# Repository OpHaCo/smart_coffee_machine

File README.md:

# Coffee machine Hack

Project has been done in Amiqual4Home Equipex Creativity Lab - https://amiqual4home.inria.fr/
We worked with ENSIMAG students of ["café sourire project"](http://fablab.ensimag.fr/index.php/Machine_%C3%A0_caf%C3%A9_%22sourire%22_:_Machine_connect%C3%A9_qui_offre_des_caf%C3%A9s_aux_personnes_souriantes)  

*To hack : Saeco Intelia Coffee Machine*

## **Description**
**You purchased a Saeco Intelia coffee machine. You are very satisfied with it, but you would like to make your coffee from your bedroom just after you wake up...** 

Some other products can do it for you : http://smarter.am/coffee/ . But with Smarter coffee machine you will have to change Coffee filter each time you get a coffee. With an "automatic" coffee machine such as Intelia, coffee grounds are pushed to a compartment : you can do several coffee only by pushing buttons and putting a cup of coffee.

Best choice for a super automatic & connected coffee machine is Philips Saeco Gran Baristo Avanti. It is connected over bluetooth. Due to bluetooth range limitations, you won't be able to do your coffee from your bedroom. It costs 2500$!!  
[Fortune and smart coffee maker](http://fortune.com/2015/12/24/smart-coffee-maker/)

With this project you will :
 *  **make your automatic coffee machine smarter adding means to control it from anywhere**  e.g. : 
    *  prepare coffee for tomorrow morning at 8AM 
    *  give a vocal command to your smartphone that will make your coffee
    *  using a camera (refer 'Used in projects' section) to deliver coffee to identified users (refer example of 'café sourire' ) 

*Café Sourire*

 * **get coffee machine statistics such as number of coffee per day...**

*Coffee metrics*
 
 * **improve some existing parts**
    * add a bigger coffee compartment (TODO)
    * add cup detection (TODO)
    * cup distribution (TODO)

## **Prerequisities**
 * **saeco intelia coffee machine** : https://www.amazon.com/Philips-Saeco-Intelia-Automatic-Espresso/dp/B00B5M3G26
 * some screws to open coffee machine
 * An external board connected to Coffee Machine front side daugther board : 
   * a fablab access to mill PCB, print 3d parts
   * **ESP8266** 
   * **Teensy 3.1/3.2 (optional)**
   * other electronic components refer hardware part

 * A linux machine hosting an MQTT broker an hosting needed software for your use case

### **Hardware hacking**
On paper front side with its buttons and LCD sceen gives all elements to hack coffee machine :

*Coffee machine front side control panel*

We want to :
 * control machine from external MCU by sending some commands such as "Small Coffee", "Calc Clean"...
 * get coffee machine current status

#### **First analysis**
From daughterboard PCB :

*Coffee machine front side control components*

Behind display, no MCU :

**We can see** :
 * NO MCU!
 * 16 lines ribbon cable connecting motherboard and daughter board
 * 7 push buttons (PB1 to PB7) pulled up to 5V, debounced using an RC filter, (C25...) 
   * these buttons are either connected to a line of 16 line ribbon cable (PB5, , PB4, PB6) or both combined (threw resistor network) and connected to 16 line ribbon cable (PB1/PB2, PB3/PB7)
 * 18 lines display connector
 * a ChipOnGlass display - no info, datasheet can be found with COG references, except [this thread](http://www.forum-raspberrypi.de/Thread-unbekanntes-display-identifizieren)  

*COG screen*

From this first analysis, we can suppose hacking can be done only from front side daughter board :
 * **hacking existing push buttons to control coffee machine** 
 * **sniffing display lines to get coffee machine display content and so getting current status**

Coffee machine main mother board (on rear side) won't been hacked. 

#### **Buttons hack**

*Front panel buttons identification.*

We want to keep coffee machine functional, i.e. :
**coffee machine can be both controlled from buttons and remotely using and external MCU**

On several line of 16 lines ribbon cable some buttons signals are combined. In order to hack it we will not connect bipolar transistors at cable level but at button level. 

In order to achieve this, a simple solution is to use a bipolar transistor in saturation (switch). It simulates button press. It is controlled from an external MCU :  

We choose a nodemcu as external MCU.  

**Coffee machine will be controlled from WIFI using MQTT using nodemcu hardware.**

#### **Machine status**
LCD can be either red, yellow, black or green. These backlight colors are set from 3 wires (Red - White - Green) near display connector. At 16 line cable, two signals control it :
 * at pin 14 : green control ( logical 1 => green)
 * at pin 15 : red control (logical 1 => red)
Screen yellow when (pin 14, pin16) =( 1, 1)

Reading on these lines using a digital input can be useful to get coffee machine error status.
In order to get more info, LCD screen must be analyzed.

#### **Chip On Glass hack**
Coffee machine status is displayed on LCD...  If we hack LCD to get displayed content we will get coffee machine status.

No COG datasheet can be found from display references. Reading some other COG datasheet gave some useful info : most of the time it is controlled using SPI / I2C.
Most of the LCD lines are connected to GND threw a capacitor. But other lines are interesting...
Using logic analyser on display connector lines gives some useful information. It looks like SPI with these characteristics :
 * 2.5MHz clock
 * CPOL = 1
 * CPHA = 1

Some capture are in ./hardware/logic_capture/

Some SPI bursts are sent at fixed interval :

*SPI burst*

*SPI byte transmission in a burst*

From this we can get more info about daughter / mother board 16 lines connector : 

**How to identify a coffee machine status from some SPI bytes?**

An intuitive solution is to find some unique patterns in SPI bytes when coffee machine displays a specific content. 

**How can my external MCU sniff SPI traffic?**
 * it must be configured as an SPI slave and read incoming bytes
 * incoming bytes are computed to identify some given patterns

 * on arduino uno : SPI slave is not supported using Arduino delivered libraries. Fortunately, Nick Gammon releases an SPI library supporting [SPI slave on Atmega328p](http://www.gammon.com.au/forum/?id=10892) 
Finding some simple patterns from SPI slave bytes can be done... but it is too slow. A simple test is to echo a rising edge/falling edge when a byte is received. It is done by manipulating directly GPIO register e.g.:
    
        // set pin 4 to HIGH
        PORTD |= 1 << 4;
        // set pin 4 to LOW
        PORTD &= ~(1 << 4);

such a simple echo takes 5.4µs between two consecutive edges, it must be compared with a byte transmisssion time @2.5MHz = 8x1/2.5M = 3.2µs. We won't be able to compute precisely some pattern from SPI bytes. Too many data are lost during IT handling.    
 * on an ESP8266 : SPI slave conflicts with flash memory, HSPI must be used http://bbs.espressif.com/viewtopic.php?t=77 . Not tested.
 * on Teensy 3.1/3.2, SPI slave library is included in Arduino Core. After testing, it is possible to compute SPI bytes to identify predefined patterns. **We will use this board to detect coffee machine status** 

##### **Pattern identification**
In order to find unique patterns in SPI data for a given LCD displayed status :
 * some logic captures are done for each LCD displayed status using Salae logic analyzer
 * these captures ared decoded using SPI analyser and exported to CSV, some captures are available under : 
     
        ./hardware/logic_capture/SPI_decoded
 * SPI decoded files are computed using :
     * a bash script (very slow - given as exemple) located in 
        
                ./hardware/logic_capture/tools/get_pattern.sh 

     * or a python script, bash script was too slow

                ./hardware/logic_capture/tools/get_pattern.py

Te find unique pattern of minimum 2 bytes only present when a middle amount of coffee is displayed on screen :

        ./hardware/logic_capture/tools/get_pattern.py ./hardware/logic_capture/SPI_decoded/off.txt ./hardware/logic_capture/SPI_decoded/*.txt 2
        Try to find a unique pattern for a pattern size of 2
        new pattern [240 224 ] is unique - nb occurences = 162
        new pattern [128 128 ] is unique - nb occurences = 216
        new pattern [15 15 ] is unique - nb occurences = 378
 
It can be confirmed using : 

        pcregrep -c -M  '15\n.*15\n' ./hardware/logic_capture/SPI_decoded/*.txt

In some cases pattern identification using Salae logig files gives unique pattern results that are not detected on Teensy case. For these special cases, I suggest sniffing SPI with Teensy and applying get_pattern.py to traces. Here is an example that shows this issue :
I want to get middle coffee unique pattern :

    ./hardware/logic_capture/tools/get_pattern.py ./SPI_decoded/medium_coffee.txt ./SPI_decoded/*.txt 4
    Try to find a unique pattern for a pattern size of 4
    new pattern [0 0 128 96 ] is unique - nb occurences = 17
    new pattern [24 12 228 52 ] is unique - nb occurences = 40
    new pattern [3 0 0 240 ] is unique - nb occurences = 58

Adding :

    {MEDIUM_COFFEE,   {.pattern32 = PATTERN_32(240, 0, 0, 3)}, UINT32, "MEDIUM_COFFEE"}

to patterns table in :

    ./embedded_software/saeco_intelia_hack/saeco_status/saeco_status.ino

do not give any results. In this case, direct SPI sniffing using teensy is needed. You have to flash :

    ./embedded_software/saeco_intelia_hack/saeco_display_sniffer/saeco_display_sniffer

then sniff SPI in medium coffee state, save UART stream to  and then apply :

    ./hardware/logic_capture/tools/get_pattern.py ./SPI_decoded_teensy/medium_coffee.txt ./SPI_decoded_teensy/*.txt 8
    Try to find a unique pattern for a pattern size of 8
    new pattern [224 248 248 240 192 0 15 24 ] is unique - nb occurences = 230

and then add:

    {MEDIUM_COFFEE,   {.pattern64 = PATTERN_64(14, 56, 48, 24, 15, 0, 192, 240)}, UINT64, "MEDIUM_COFFEE"} 

to patterns table in :

    ./embedded_software/saeco_intelia_hack/saeco_status/saeco_status.ino

#### **PCB design**
Design files are under : 

    ./hardware/pcb_design/

#### **PCB integration**

PCB is integrated on coffee machine right side. Here is an integration with hack mother board and hack status board (get status over LCS SPI and LCD backlight leds)

### **general architecture**

### **software**
Library to add is located under :

    ./embedded_software/saeco_intelia_hack/

Under : 

    ./embedded_software/saeco_intelia_hack/saeco_hack_example/saeco_hack_example.ino

You will find an example where coffee machine is controlled remotely using MQTT protocol (refer "Commands" section"). Button presses published to MQTT (refer Events section).
Firmware uploader Over The Air  

Under :

    ./embedded_software/saeco_intelia_hack/saeco_status/saeco_status.ino

You will find Teensy 3.x code to get Saeco Intelia current status (from LCD lines).

Under :

    ./embedded_software/saeco_intelia_hack/saeco_display_sniffer/saeco_display_sniffer.ino

You will find Teens 3.x code that sniffs SPI lines and display captured buffer.
#### **Commands**
Coffee machine controlled using MQTT protocol. 

##### **MQTT topics** 
Here are MQTT topics for example given in : 

    ./embedded_software/saeco_intelia_hack/saeco_hack_example/    

- **"/amiqual4home/machine_place/saeco_intelia/smallCoffee"** : sending any byte to this value will simulate a short press on smallCoffee button

- **"/amiqual4home/machine_place/saeco_intelia/Coffee"**   : sending any byte to this value will simulate a short press on coffee button

- **"/amiqual4home/machine_place/saeco_intelia/power"**     : sending any byte to this value will simulate a short press on power button

- **"/amiqual4home/machine_place/saeco_intelia/brew"**      : sending any byte to this value will simulate a short press on brew button

- **"/amiqual4home/machine_place/saeco_intelia/tea"**       : sending any byte to this value will simulate a short press on tea button

- **"/amiqual4home/machine_place/saeco_intelia/clean"**     : sending any byte to this value will simulate a short press on clean button

- **"/amiqual4home/machine_place/saeco_intelia/getStatus"** : when it receives this command, coffee machine hack send its status

Get a small coffee over MQTT :

    mosquitto_pub -h MQTT_BROKER_IP -t /amiqual4home/machine_place/saeco_intelia/on_button_press/smallCoffee -m 1

#### **Events**

##### Button press events
Buttons press events are send threw MQTT. Here are events MQTT topic for example given in :

    ./embedded_software/saeco_intelia_hack/saeco_hack_example/   

Button press topics messages payload contains press duration in ms. 

- **"/amiqual4home/machine_place/saeco_intelia/on_button_press/powerButton"**        : power button pressed
 
- **"/amiqual4home/machine_place/saeco_intelia/on_button_press/Coffee"**             : coffee button pressed
 
- **"/amiqual4home/machine_place/saeco_intelia/on_button_press/smallCoffee"**        : small coffee button pressed
 
- **"/amiqual4home/machine_place/saeco_intelia/on_button_press/brew"**               : brew coffee button pressed
 
Example to subscribe all button press events :

        mosquitto_sub -v -h MQTT_BROKER_IP -p 1883 -t /amiqual4home/machine_place/saeco_intelia/on_button_press/#

##### Coffee machine status event
Saeco coffee machine status sent on this topic :

 - **"/amiqual4home/machine_place/saeco_intelia/status**

```
    OFF                     = 0,
    CALC_CLEAN              = 1,
    NO_WATER                = 2,
    WATER_CHANGE            = 3,
    WEAK_COFFEE             = 4,
    MEDIUM_COFFEE           = 5,
    STRONG_COFFEE           = 6,
    SPOON_COFFEE            = 7,
    DOOR_OPEN               = 8,
    COFFEE_GROUND_OPEN      = 9,
    NO_COFFEE_WARNING       = 10,
    NO_COFFEE_ERROR         = 11,
    UNKNOWN_OK              = 12,
    UNKNOWN_WARNING         = 13,
    UNKNOWN_ERROR           = 14,
    COFFEE_GROUND_FULL      = 15
```

Here are coffee machine statuses :

When application starts it sends an alive message on topic : 

 - **"/amiqual4home/machine_place/saeco_intelia/alive"**

#### Openhab
[Openhab](http://www.openhab.org/) is used to interface with coffee machine. From a web interface you can control machine and get current status.

## **Used in projects**
 * [café sourire](http://fablab.ensimag.fr/index.php/Machine_%C3%A0_caf%C3%A9_%22sourire%22_:_Machine_connect%C3%A9_qui_offre_des_caf%C3%A9s_aux_personnes_souriantes)

*Café Sourire*

 * refer gateway_software/examples
 * coffee_machine_metrics : get coffee machine usage 

*Coffee metrics*

## **References**
http://www.gammon.com.au/forum/?id=10892
https://www.saleae.com
http://fablab.ensimag.fr/index.php/Machine_%C3%A0_caf%C3%A9_%22sourire%22_:_Machine_connect%C3%A9_qui_offre_des_caf%C3%A9s_aux_personnes_souriantes

## **TODO**
* Ajouter capture arduino UNO et SPI
*Detection et mise en place tasse
*Detection debordement eau
*Hack mecanique : plus grands compartiments

## **Thanks to**
ENSIMAG "café sourire" students http://fablab.ensimag.fr/index.php/Machine_%C3%A0_caf%C3%A9_%22sourire%22_:_Machine_connect%C3%A9_qui_offre_des_caf%C3%A9s_aux_per    sonnes_souriantes

## **License**
 smart_coffee_machine (c) by Lahorde mr.lahorde@laposte.net
 smart_coffee_machine is licensed under a
 Creative Commons Attribution-NonCommercial 3.0 Unported License.

 You should have received a copy of the license along with this
 work.  If not, see <http://creativecommons.org/licenses/by-nc/3.0/>.

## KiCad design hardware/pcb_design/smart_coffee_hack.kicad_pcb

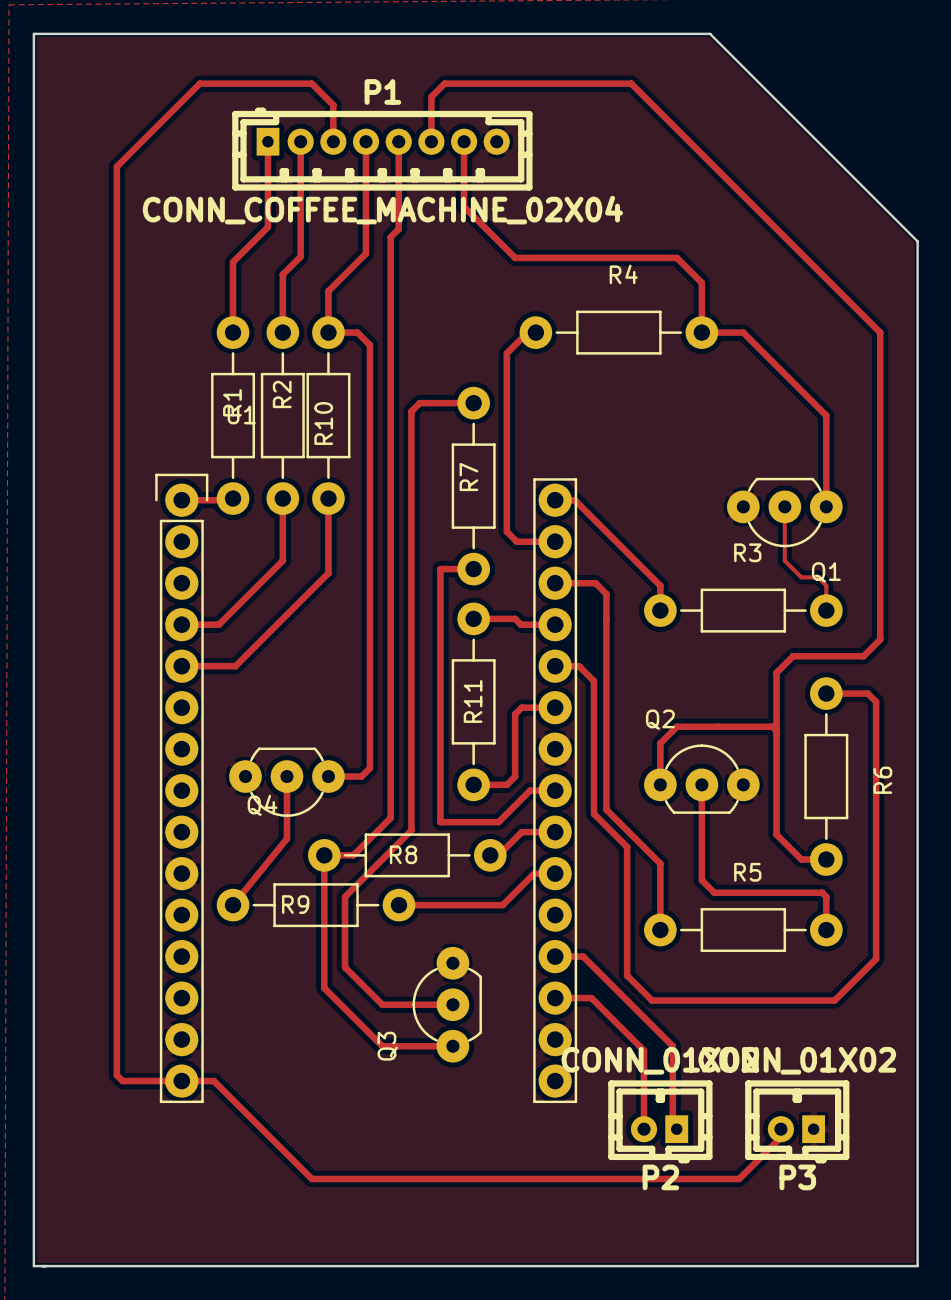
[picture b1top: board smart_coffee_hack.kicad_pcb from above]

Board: 2 copper layers, 54.1 x 75.4 mm, 19 parts (0 on the bottom side), 26 nets.

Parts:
P1: CONN_COFFEE_MACHINE_02X04; b8b-ph-kl
P2, P3: CONN_01X02; b2b-ph-kl
Q1, Q2, Q3, Q4: BC547; TO-92_Inline_Wide
R1, R2, R3, R4, R5, R6, R7, R8, R9, R10, R11: R; Resistor_Horizontal_RM10mm
U1: NodeMCU_Amica_R2

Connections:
+3V3: R11.1, U1.16, U1.25
+5V: P1.3, P3.2, U1.15
GND: P1.8, P3.1, Q1.3, Q2.3, Q3.3, Q4.3, U1.10, U1.14, U1.17, U1.24
unnamed: P1.1, R1.2
unnamed: P1.2, R2.2
unnamed: P1.4, Q4.1, R10.2
unnamed: P1.5, Q3.1, R8.2
unnamed: P1.6, Q2.1, R6.2
unnamed: P1.7, Q1.1, R4.2
unnamed: P2.1, U1.19
unnamed: P2.2, U1.18
unnamed: Q1.2, R3.2
unnamed: Q2.2, R5.2
unnamed: Q3.2, R7.2
unnamed: Q4.2, R9.2
unnamed: R1.1, U1.1
unnamed: R2.1, U1.4
unnamed: R3.1, U1.30
unnamed: R4.1, U1.29
unnamed: R5.1, U1.28
unnamed: R6.1, U1.26
unnamed: R7.1, U1.23
unnamed: R8.1, U1.22
unnamed: R9.1, U1.21
unnamed: R10.1, U1.5
unnamed: R11.2, U1.27

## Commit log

2016-05-26 First delivery of saeco intelia hack
2016-05-26 Add an example
2016-05-27 Added esp8266 Arduino with mqtt example
2016-05-27 Add coffee control over MQTT
2016-06-02 debug on button callback
2016-06-02 enable OTA and check for button rebound
2016-06-02 merge
2016-06-03 add ota
2016-06-10 correct pin and more callbacks
2016-06-10 add saeco_intelia
2016-06-14 Add some missing functions
2016-06-14 Add last version of example from issue #3
2016-06-14 bad topic for power
2016-06-14 Better button press detection
2016-06-14 Add scope captures
2016-06-14 Fix startup errors at startup after multiple MQTT client api calls
2016-06-15 Add coffee metrics application
2016-06-17 Squashed 'hardware/pcb_design/additional_components/stavros-kicad-components/' content from commit 888a47e
    git-subtree-dir: hardware/pcb_design/additional_components/stavros-kicad-components
    git-subtree-split: 888a47ec0d75921a9c1fc3e0a370f151ceb32d3c
2016-06-17 Add pcb schematic
2016-06-17 Add pcb
2016-06-24 Add draft of SPI slave COG display sniffer on teensy
2016-07-12 Add files to decode pattern
2016-07-12 add some imgs
2016-07-13 Add doc images
2016-07-13 Minor modif
2016-07-13 bad file name
2016-07-18 Add img
2016-07-20 Add SPI display sniffer. Add LCD pattern detector to get status of saeco in saeco_status
2016-07-21 Compute status from LCD lines + backlight. Communication between status getter and its motherboard
2016-07-22 Update kicad component. Update doc.
2016-07-22 Status handling. Same name for button press / button simulation MQTT topics suffixes
2016-07-22 minor modif in doc
2016-07-22 PCB modification
2016-07-26 Update example according to PCB
2016-07-26 Add Saeco gran baristo avanti reference
2016-07-26 Add cafe sourire example application
2016-07-27 Modify openhab config. Remove vim swap files
2016-07-27 minor modif for build
2016-07-28 Debug + Test
2016-07-28 file rename
2016-07-29 Override time in daily singlestat
2016-08-01 Squashed 'gateway_software/examples/CafeSourire/detect_smile_python/' content from commit e1dd8c5
    git-subtree-dir: gateway_software/examples/CafeSourire/detect_smile_python
    git-subtree-split: e1dd8c517c1c7bbe6bc994f3cc2f153c7da43094
2016-08-01 Modif for python 3. Neighbors can be modified
2016-08-02 Add detection over frame. Detection depends on face detected size
2016-08-02 add haar cascades
2016-08-02 Make script runnable on raspberry
2016-08-02 Smile detection over MQTT
2016-08-02 nose detection was ko
2016-08-03 add openhab config files
2016-08-04 Add openhab rule to make when a smile is detected. Add topic to get coffee machine status
2016-08-04 Add face detection from opencv tuto
2016-08-30 Use openhab to display last button press date
2016-08-30 Capture in a separate thread. Dynamically add training imgs for face recognition
2016-08-31 Capture training frame using MQTT
2016-09-02 Add prediction confidence, mqtt async connection
2016-09-07 Clean CafeSourire folder
2016-09-07 Increase rpi resolution. Add some constants
2016-09-07 Set resolution on non rpi webcam
2016-09-07 Add/clean items needed for demo.
2016-09-07 Add hello message on power on
2016-09-08 Add goodbye message
2016-09-15 Add LBPH model for face rec
2016-09-16 Add donald. bug in PowerOn/Off sound
2016-09-30 Always restart service
2016-10-05 Add yappi profiling tools in multithreaded context
2016-10-05 Add yappi formatted logs to profiling. Modify default min window for multiScale detection
2016-10-06 Capture - Detect thread synchro using double buffering
2016-10-06 Add mapping user <-> Coffee type
2016-10-06 Do not power machine if user do not take any coffee. Missing map file
2016-10-07 Play custom music. Hello bug. Exit smile rule if user coffee setting is no coffee
2016-10-11 Add youtube thumbnail
2016-10-11 Modify youtube thumbnail
2016-10-21 Play music during coffee with fades using sox
2016-11-08 Coffee machine offers a wireless access point
2016-11-29 Use pico2wave for tts - remove old generated wav files for welcome msg
2016-12-08 Only 1 coffee given at a time : add item to control coffee making
2017-01-25 Minor updates. Exit on capture thread exit bug because of isAlive typo
2017-01-26 Add different demo configurations
2017-02-24 Workaround failing alsa software mixing when mpd is playing
2017-02-24 Add slack rules
2017-04-12 minor bugs
2017-04-26 minor modif in openhab helper scripts
2017-10-06 Be sure GPIO used to control coffee machine are well configured before doing some time consuming tasks (network connection...)
2017-10-13 opencv API renaming
2017-10-20 clean openhab config files
2017-10-20 Modif for openhab2 + clean in sounds
2017-10-20 Power on machine on face detection. Get status on openhab start
2017-10-24 Add nose detection
2018-08-30 Handle video stream with X server
